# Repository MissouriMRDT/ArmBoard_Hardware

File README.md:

# RoboticArm-Hardware
Hardware design files for robotic arm

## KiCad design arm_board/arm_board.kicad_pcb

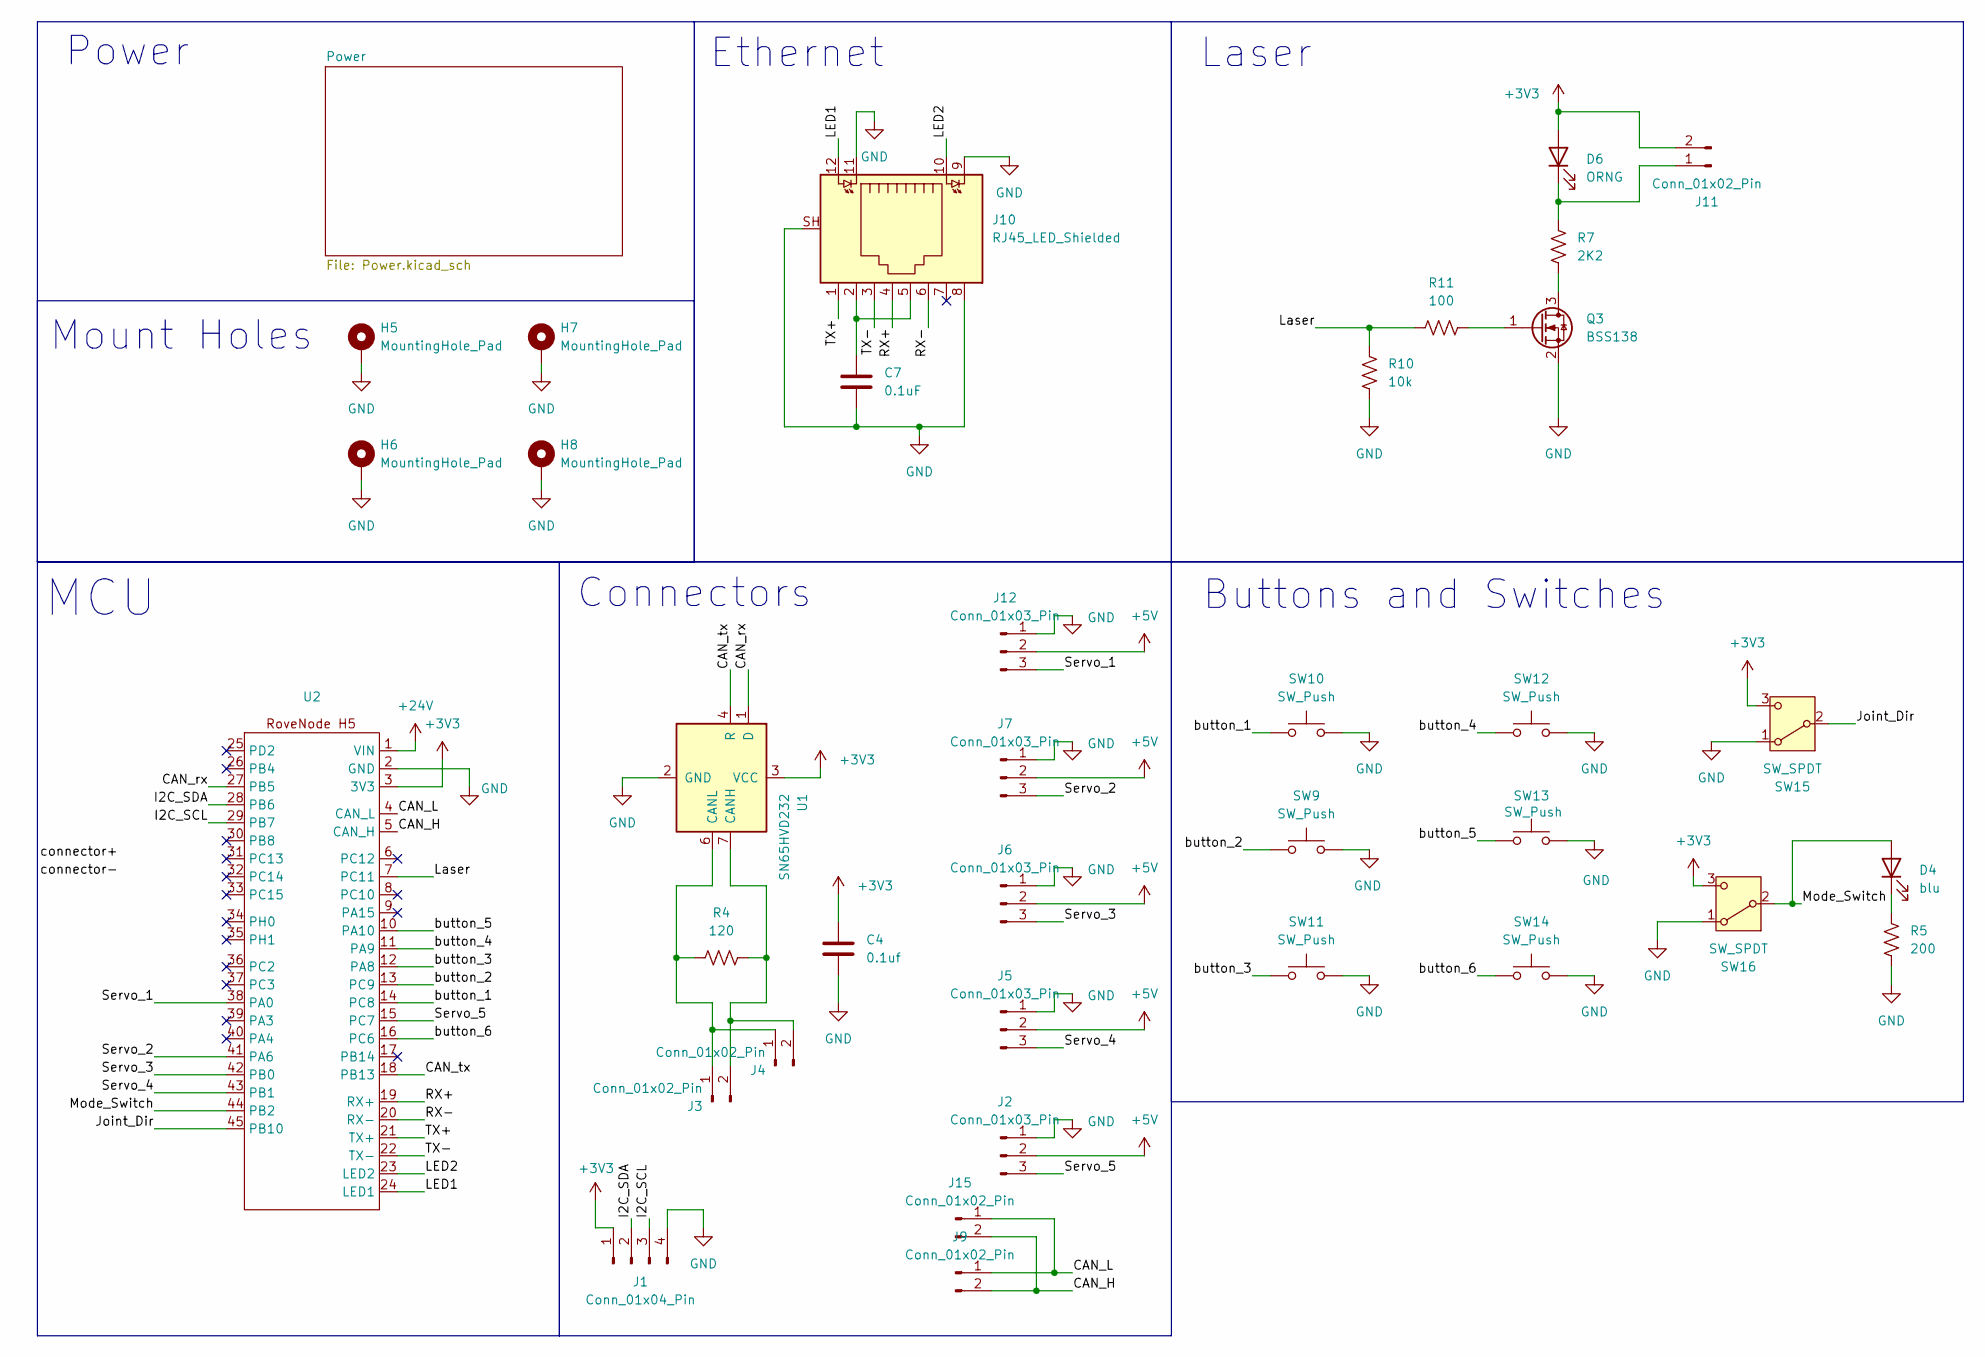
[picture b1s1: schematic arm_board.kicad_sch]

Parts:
C4: 0.1uf; C_0603_1608Metric_Pad1.08x0.95mm_HandSolder
C7: 0.1uF; C_0603_1608Metric_Pad1.08x0.95mm_HandSolder
D4: blu; LED_0603_1608Metric_Pad1.05x0.95mm_HandSolder
D6: ORNG; LED_0603_1608Metric_Pad1.05x0.95mm_HandSolder
H5, H6, H7, H8: MountingHole_Pad; 4_40_Hole_Pad_Via
J1: Conn_01x04_Pin; JST_PH_S4B-PH-K_1x04_P2.00mm_Horizontal
J2, J5, J6, J7, J12: Conn_01x03_Pin; JST_PH_S3B-PH-K_1x03_P2.00mm_Horizontal
J3, J4, J9, J11, J15: Conn_01x02_Pin; JST_PH_S2B-PH-K_1x02_P2.00mm_Horizontal
J10: RJ45_LED_Shielded; RJ45_Teensy
Q3: BSS138; SOT-23
R4: 120; R_0603_1608Metric_Pad0.98x0.95mm_HandSolder
R5: 200; R_0603_1608Metric_Pad0.98x0.95mm_HandSolder
R7: 2K2; R_0603_1608Metric_Pad0.98x0.95mm_HandSolder
R10: 10k; R_0603_1608Metric_Pad0.98x0.95mm_HandSolder
R11: 100; R_0603_1608Metric_Pad0.98x0.95mm_HandSolder
SW9, SW10, SW11, SW12, SW13, SW14: SW_Push; SW_SPST_TL3305A
SW15, SW16: SW_SPDT; SW_Slide_SPDT_Angled_CK_OS102011MA1Q
U1: SN65HVD232; SOIC-8_3.9x4.9mm_P1.27mm
U2: RoveNode_H5

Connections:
+3V3: C4.1, D6.2 (A), J1.1, J11.2, SW15.3 (C), SW16.3 (C), U1.3 (VCC), U2.3 (3V3)
+5V: J2.2, J5.2, J6.2, J7.2, J12.2; also elsewhere on the board
+24V: U2.1 (VIN); also elsewhere on the board
/CAN_H: J9.2, J15.2, U2.5 (CAN_H)
/CAN_L: J9.1, J15.1, U2.4 (CAN_L)
/CAN_rx: U1.1 (D), U2.27 (PB5)
/CAN_tx: U1.4 (R), U2.18 (PB13)
/I2C_SCL: J1.3, U2.29 (PB7)
/I2C_SDA: J1.2, U2.28 (PB6)
/Joint_Dir: SW15.2 (B), U2.45 (PB10)
/LED1: J10.12, U2.24 (LED1)
/LED2: J10.10, U2.23 (LED2)
/Laser: R10.1, R11.1, U2.7 (PC11)
/Mode_Switch: D4.2 (A), SW16.2 (B), U2.44 (PB2)
/RX+: J10.4, U2.19 (RX+)
/RX-: J10.6, U2.20 (RX-)
/Servo_1: J12.3, U2.38 (PA0)
/Servo_2: J7.3, U2.41 (PA6)
/Servo_3: J6.3, U2.42 (PB0)
/Servo_4: J5.3, U2.43 (PB1)
/Servo_5: J2.3, U2.15 (PC7)
/TX+: J10.1, U2.21 (TX+)
/TX-: J10.3, U2.22 (TX-)
/button_1: SW10.1, U2.14 (PC8)
/button_2: SW9.1, U2.13 (PC9)
/button_3: SW11.1, U2.12 (PA8)
/button_4: SW12.1, U2.11 (PA9)
/button_5: SW13.1, U2.10 (PA10)
/button_6: SW14.1, U2.16 (PC6)
GND: C4.2, C7.2, H5.1 (1_1), H6.1 (1_1), H7.1 (1_1), H8.1 (1_1), J1.4, J2.1, J5.1, J6.1, J7.1, J10.8, J10.9, J10.11, J10.SH, J12.1, Q3.2 (S), R5.2, R10.2, SW9.2, SW10.2, SW11.2, SW12.2, SW13.2, SW14.2, SW15.1 (A), SW16.1 (A), U1.2 (GND), U2.2 (GND); also elsewhere on the board
unnamed: C7.1, J10.2, J10.5
unnamed: D4.1 (K), R5.1
unnamed: D6.1 (K), J11.1, R7.1
unnamed: J3.1, J4.1, R4.2, U1.6 (CANL)
unnamed: J3.2, J4.2, R4.1, U1.7 (CANH)
unnamed: Q3.3 (D), R7.2
unnamed: Q3.1 (G), R11.2

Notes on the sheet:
Power
Connectors
Ethernet
MCU
Laser
Buttons and Switches
Mount Holes

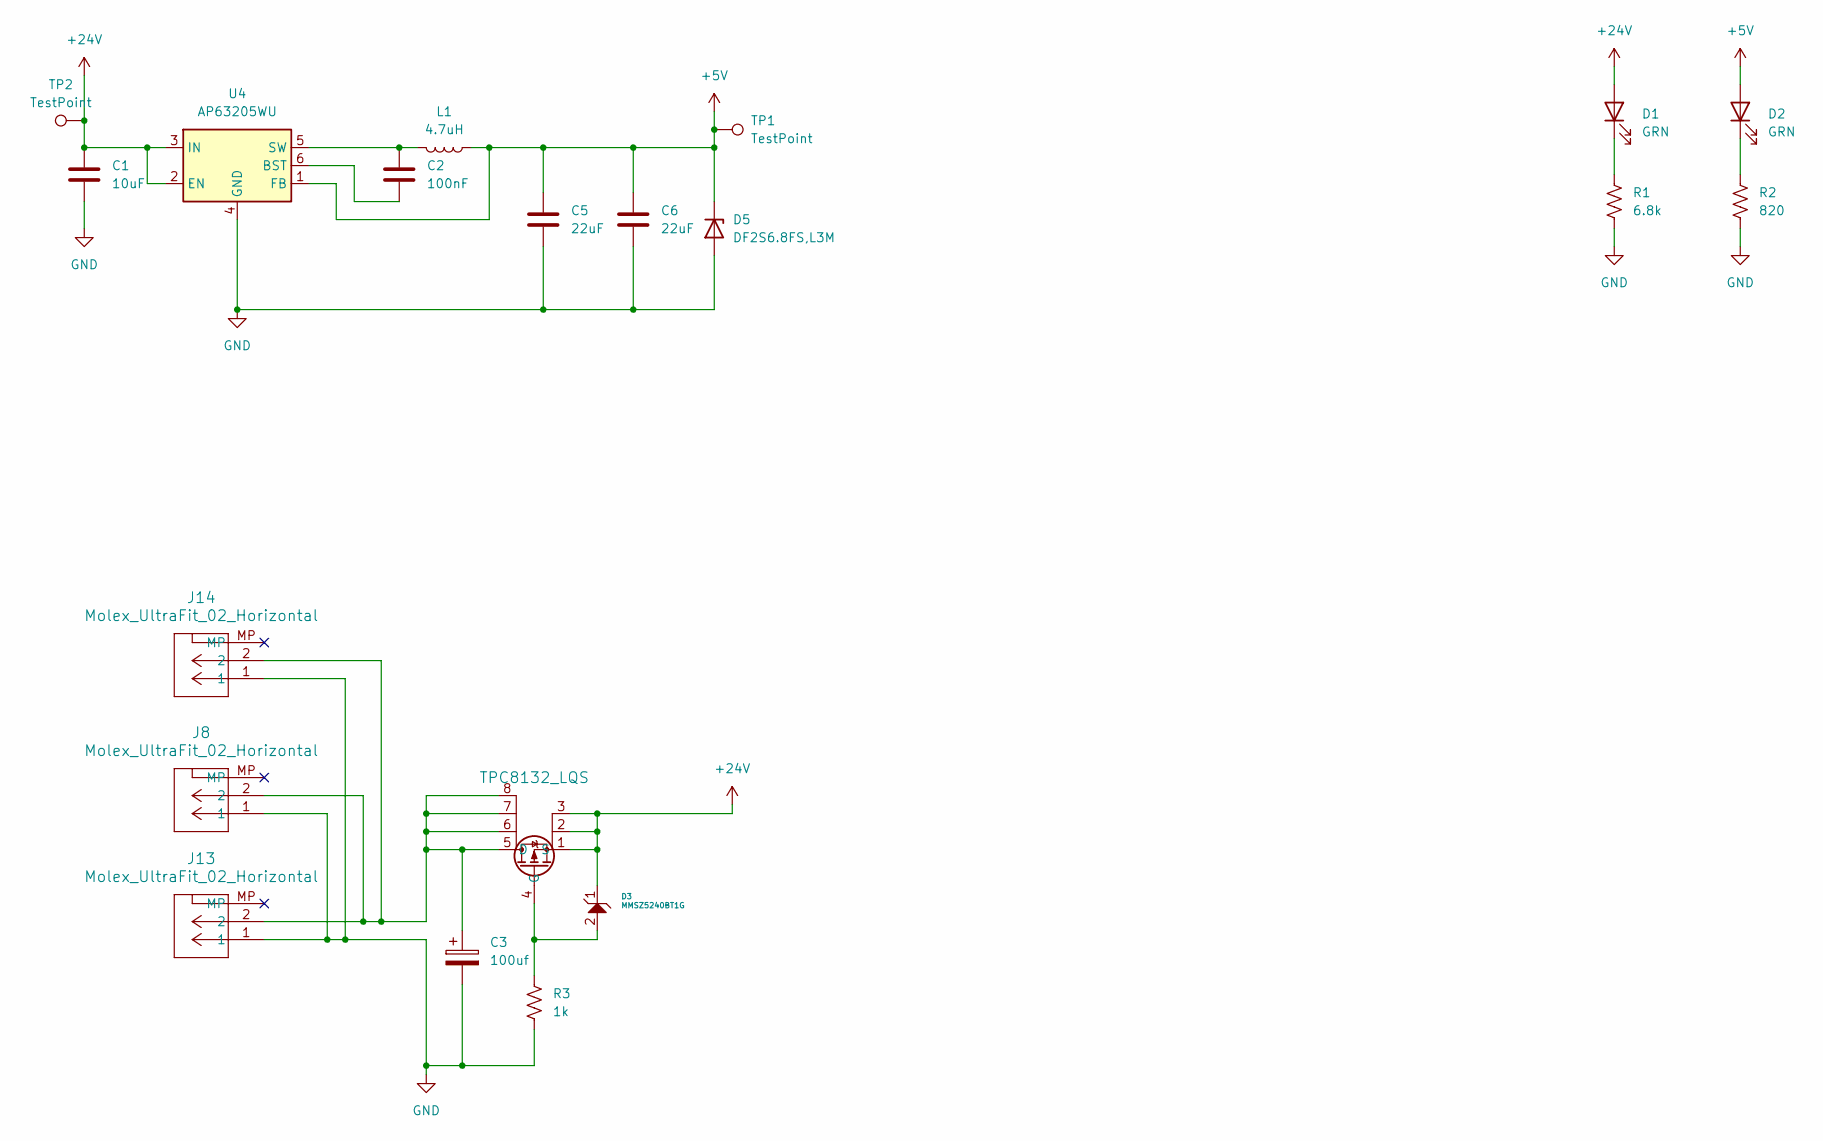
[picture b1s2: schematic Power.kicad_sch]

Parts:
C1: 10uF; C_0603_1608Metric_Pad1.08x0.95mm_HandSolder
C2: 100nF; C_0603_1608Metric_Pad1.08x0.95mm_HandSolder
C3: 100uf; CP_Radial_D6.3mm_P2.50mm
C5, C6: 22uF; C_0603_1608Metric_Pad1.08x0.95mm_HandSolder
D1, D2: GRN; LED_0603_1608Metric_Pad1.05x0.95mm_HandSolder
D3: MMSZ5240BT1G; SOD-123_ONS-L
D5: DF2S6.8FS,L3M; SOD-323_1P8X1P35_ONS
J8, J13, J14: Molex_UltraFit_02_Horizontal; MOLEX_MegaFit_02_Horizontal; MPN 1723102000
L1: 4.7uH; IND_DFE322520FD-4R7M=P2_MUR
MOSFET1: TPC8132_LQS; SOP-8_TOS-L
R1: 6.8k; R_0603_1608Metric_Pad0.98x0.95mm_HandSolder
R2: 820; R_0603_1608Metric_Pad0.98x0.95mm_HandSolder
R3: 1k; R_0603_1608Metric_Pad0.98x0.95mm_HandSolder
TP1, TP2: TestPoint; TestPoint_Pad_1.5x1.5mm
U4: AP63205WU; TSOT-23-6_HandSoldering

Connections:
+5V: C5.1, C6.1, D2.2 (A), D5.1 (K), L1.1, TP1.1 (1_1), U4.1 (FB); also elsewhere on the board
+24V: C1.1, D1.2 (A), D3.1, MOSFET1.1 (S), MOSFET1.2, MOSFET1.3, TP2.1 (1_1), U4.2 (EN), U4.3 (IN); also elsewhere on the board
GND: C1.2, C3.2, C5.2, C6.2, D5.2 (A), J8.1, J13.1, J14.1, R1.2, R2.2, R3.2, U4.4 (GND); also elsewhere on the board
unnamed: D1.1 (K), R1.1
unnamed: D2.1 (K), R2.1
unnamed: C3.1, J8.2, J13.2, J14.2, MOSFET1.5 (D), MOSFET1.6, MOSFET1.7, MOSFET1.8
unnamed: D3.2, MOSFET1.4 (G), R3.1
unnamed: C2.2, U4.6 (BST)
unnamed: C2.1, L1.2, U4.5 (SW)

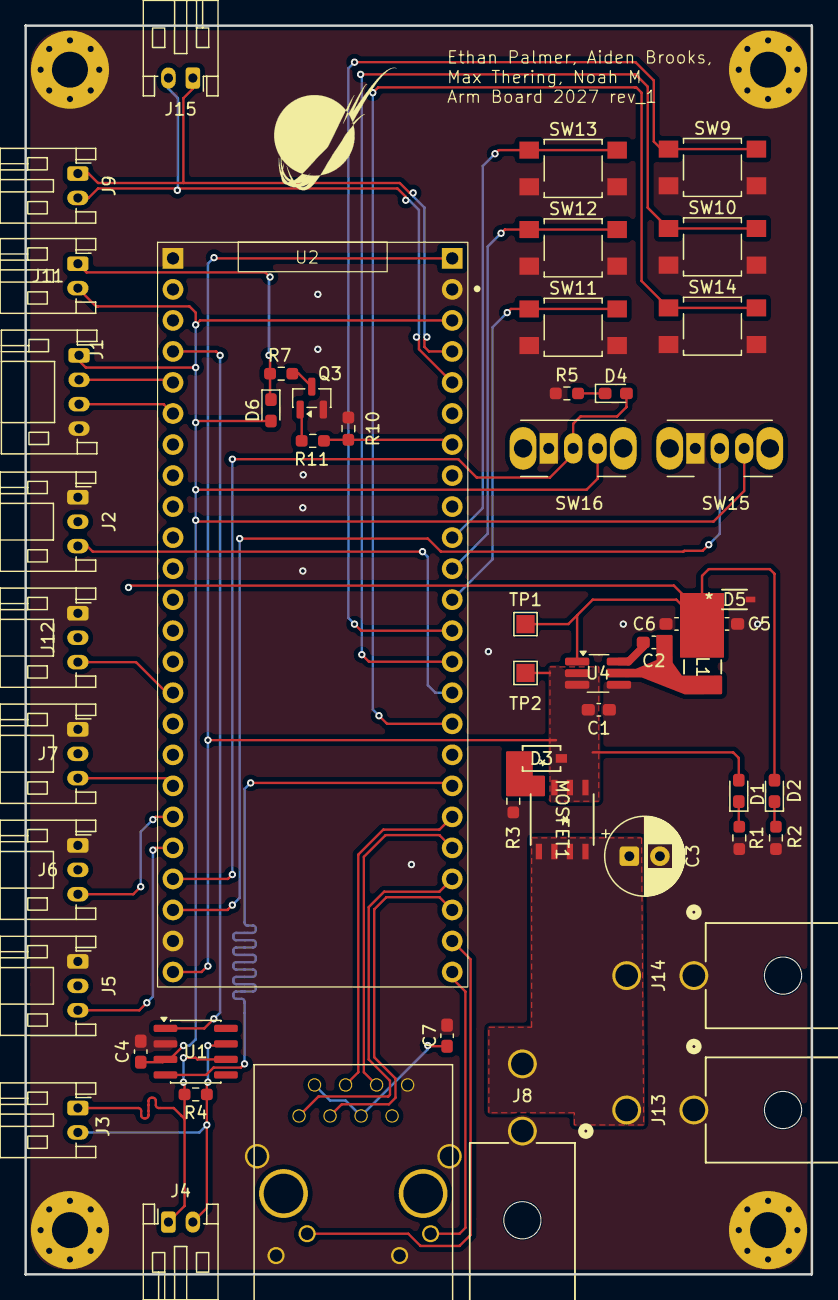
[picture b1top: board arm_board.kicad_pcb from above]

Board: 2 copper layers, 64.4 x 102.2 mm, 56 parts (0 on the bottom side), 43 nets.

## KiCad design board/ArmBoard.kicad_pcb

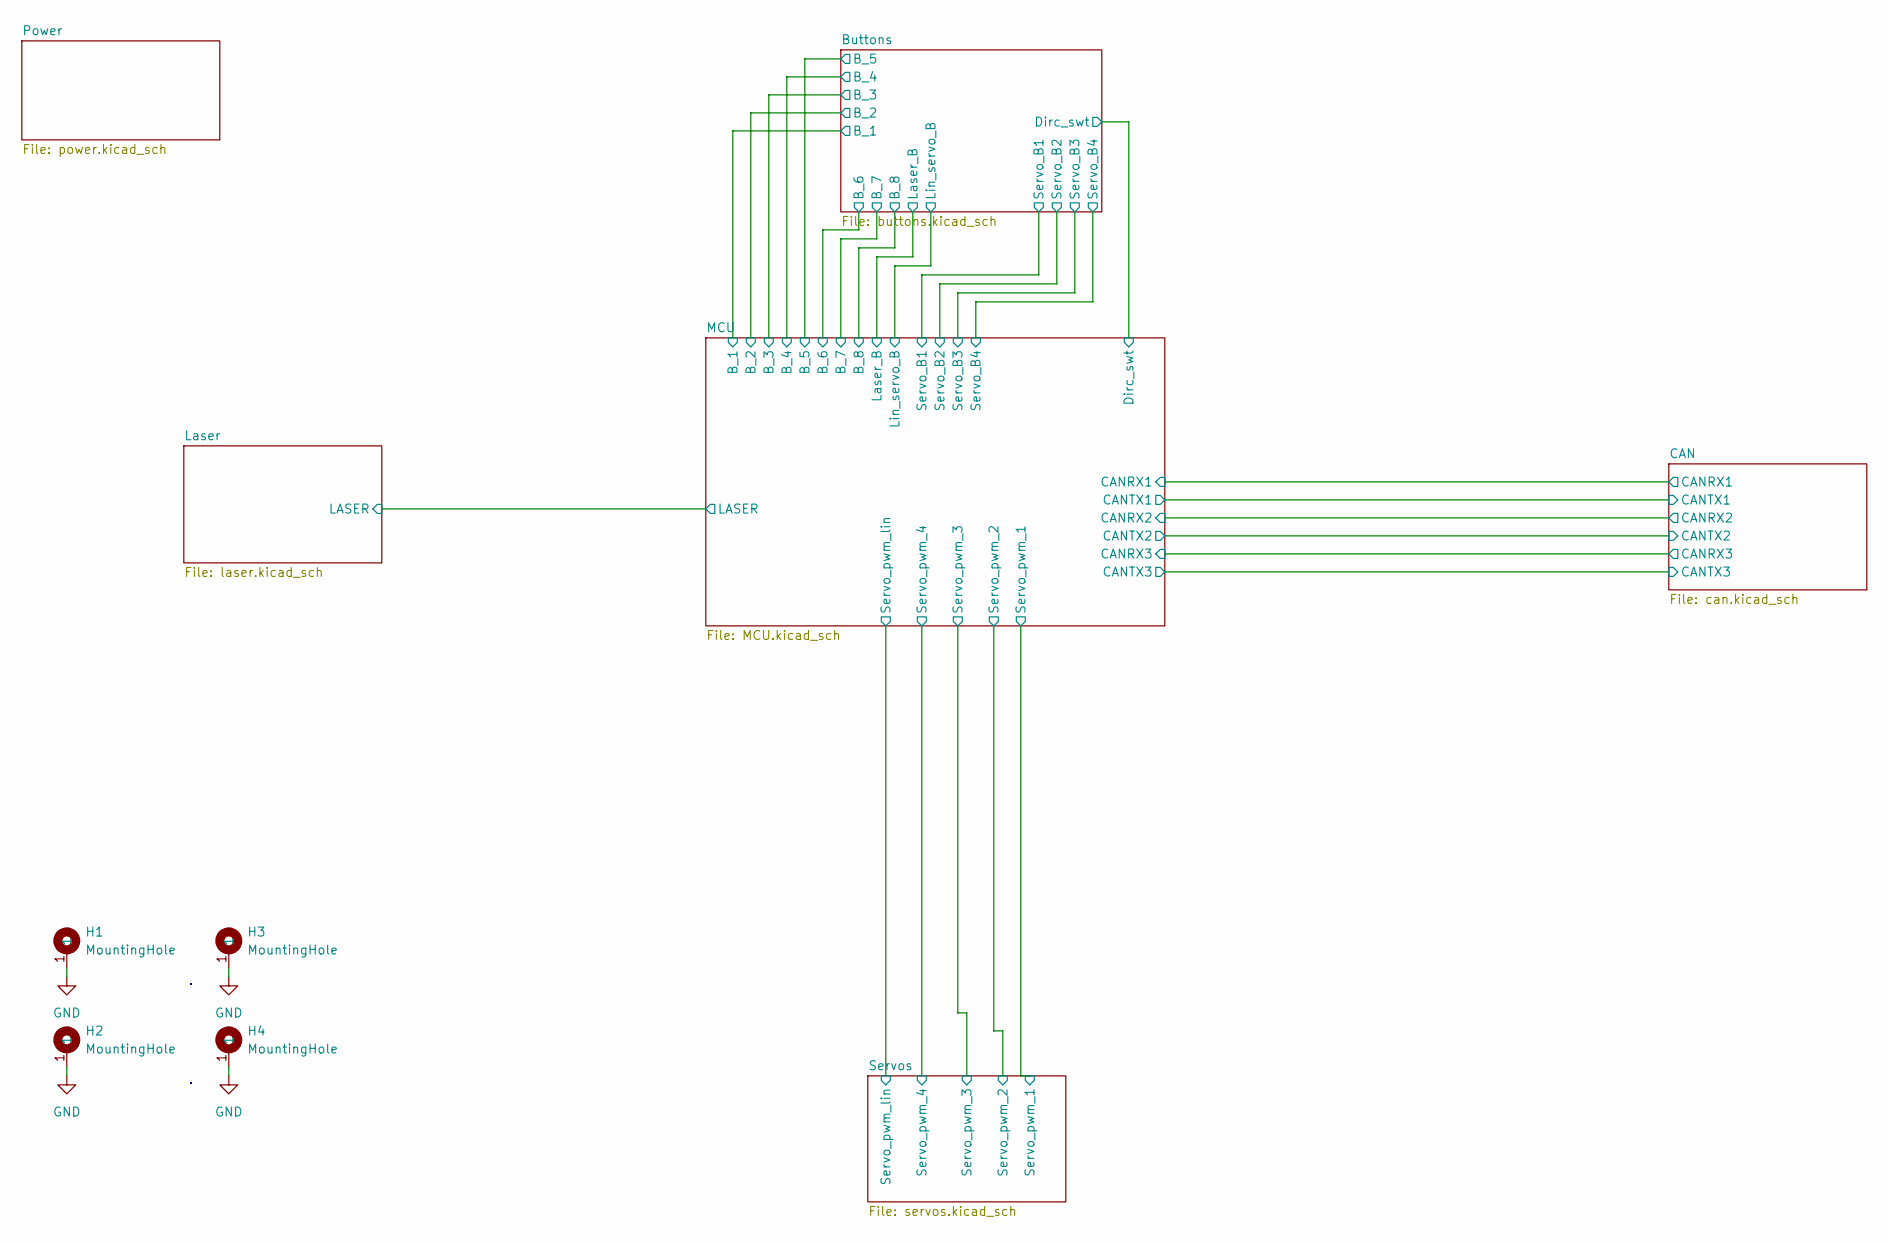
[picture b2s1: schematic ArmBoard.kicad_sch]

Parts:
H1, H2, H3, H4: MountingHole; 4_40_Hole_Pad_Via

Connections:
GND: H1.1, H2.1, H3.1, H4.1; also elsewhere on the board

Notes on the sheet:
Penis

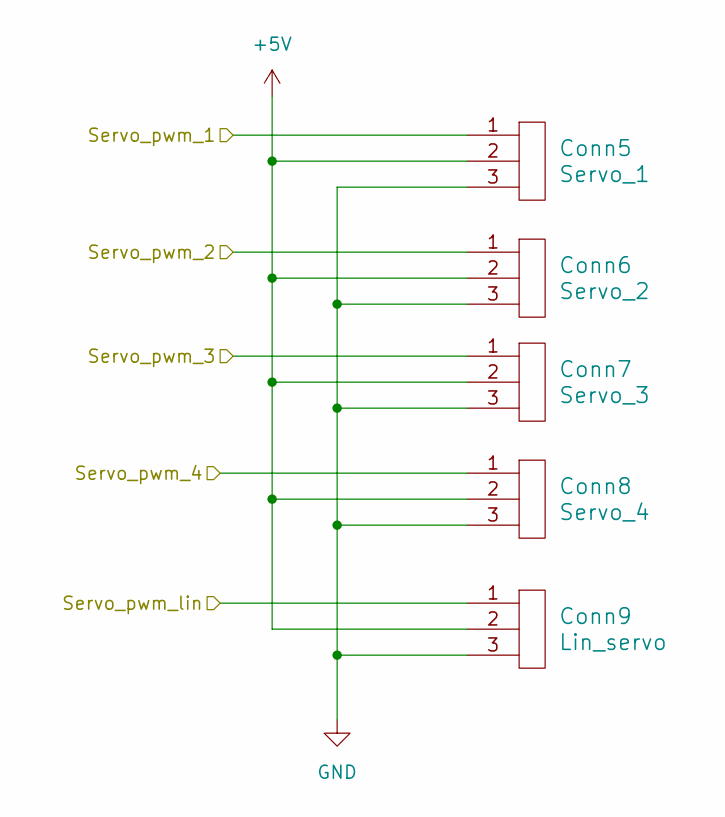
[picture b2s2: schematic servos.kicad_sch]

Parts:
Conn5: Servo_1; MOLEX_SL_03_Vertical
Conn6: Servo_2; MOLEX_SL_03_Vertical
Conn7: Servo_3; MOLEX_SL_03_Vertical
Conn8: Servo_4; MOLEX_SL_03_Vertical
Conn9: Lin_servo; MOLEX_SL_03_Vertical

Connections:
+5V: Conn5.2, Conn6.2, Conn7.2, Conn8.2, Conn9.2; also elsewhere on the board
/MCU/Servo_pwm_1: Conn5.1; also elsewhere on the board
/MCU/Servo_pwm_2: Conn6.1; also elsewhere on the board
/MCU/Servo_pwm_3: Conn7.1; also elsewhere on the board
/MCU/Servo_pwm_4: Conn8.1; also elsewhere on the board
/MCU/Servo_pwm_lin: Conn9.1; also elsewhere on the board
GND: Conn5.3, Conn6.3, Conn7.3, Conn8.3, Conn9.3; also elsewhere on the board

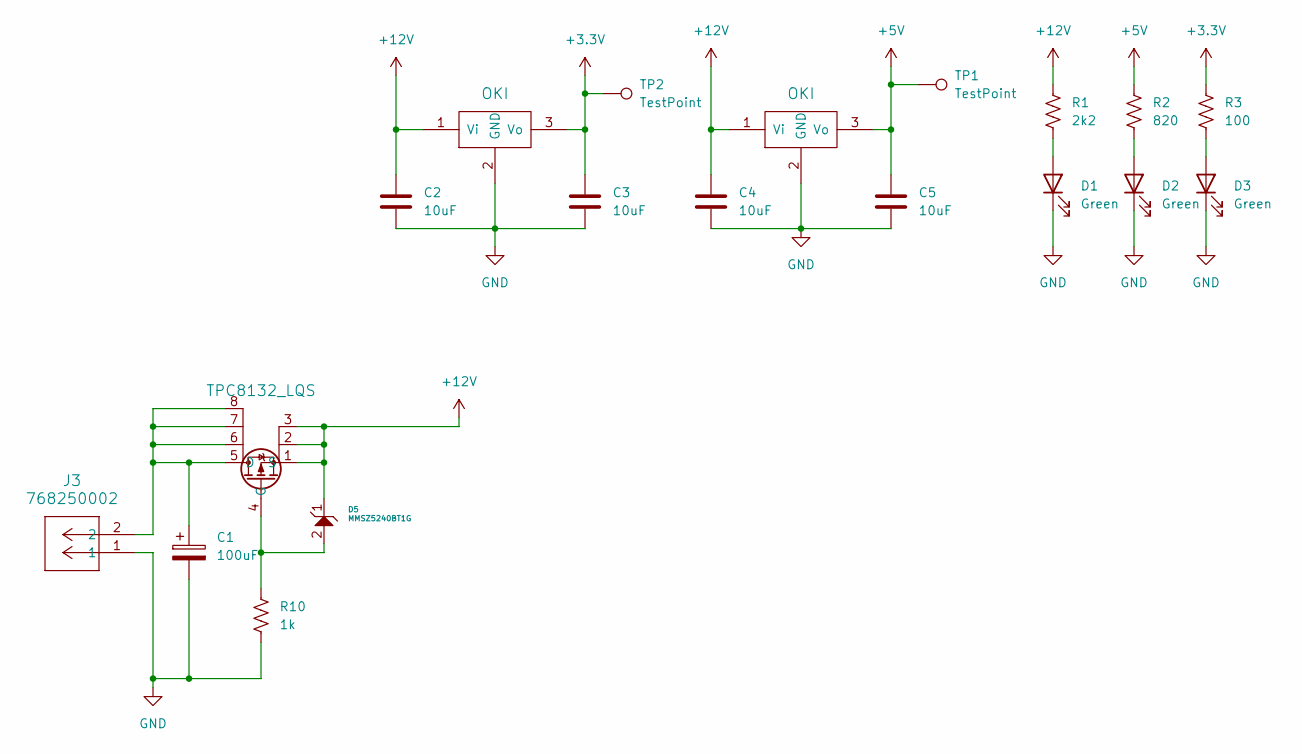
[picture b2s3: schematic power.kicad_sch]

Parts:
C1: 100uF; CP_Radial_D6.3mm_P2.50mm
C2, C3, C4, C5: 10uF; C_0603_1608Metric_Pad1.08x0.95mm_HandSolder
D1, D2, D3: Green; LED_0603_1608Metric_Pad1.05x0.95mm_HandSolder
D5: MMSZ5240BT1G; SOD-123_ONS-L
J3: 768250002; MOLEX_MegaFit_02_Horizontal
MOSFET1: TPC8132_LQS; SOP-8_TOS-L
R1: 2k2; R_0603_1608Metric_Pad0.98x0.95mm_HandSolder
R2: 820; R_0603_1608Metric_Pad0.98x0.95mm_HandSolder
R3: 100; R_0603_1608Metric_Pad0.98x0.95mm_HandSolder
R10: 1k; R_0603_1608Metric_Pad0.98x0.95mm_HandSolder
TP1, TP2: TestPoint; TestPoint_Pad_1.5x1.5mm
U2, U3: OKI; OKI_Horizontal

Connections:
+3.3V: C3.1, R3.1, TP2.1, U2.3 (Vo); also elsewhere on the board
+5V: C5.1, R2.1, TP1.1, U3.3 (Vo); also elsewhere on the board
+12V: C2.1, C4.1, D5.1, MOSFET1.1 (S), MOSFET1.2, MOSFET1.3, R1.1, U2.1 (Vi), U3.1 (Vi)
GND: C1.2, C2.2, C3.2, C4.2, C5.2, D1.1 (K), D2.1 (K), D3.1 (K), J3.1, R10.2, U2.2 (GND), U3.2 (GND); also elsewhere on the board
unnamed: D1.2 (A), R1.2
unnamed: D2.2 (A), R2.2
unnamed: D3.2 (A), R3.2
unnamed: C1.1, J3.2, MOSFET1.5 (D), MOSFET1.6, MOSFET1.7, MOSFET1.8
unnamed: D5.2, MOSFET1.4 (G), R10.1

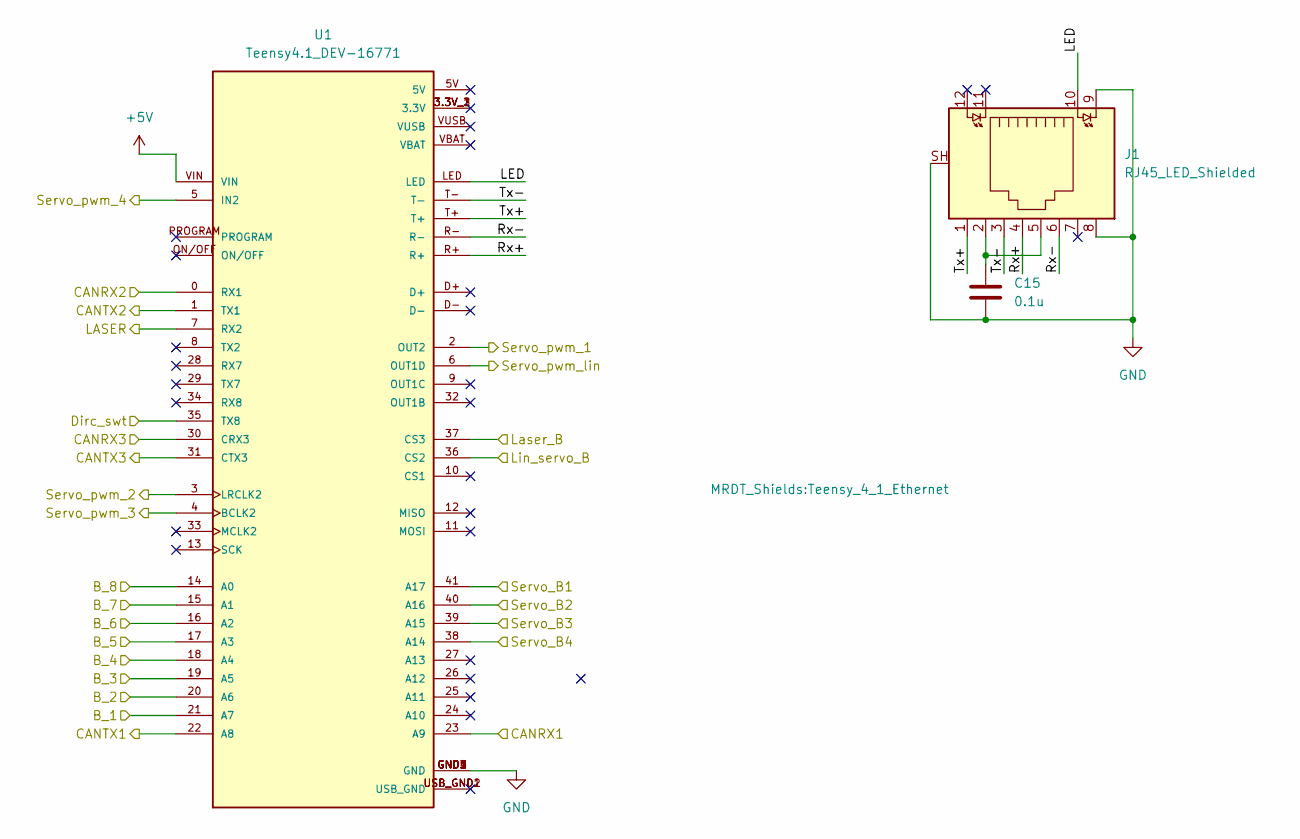
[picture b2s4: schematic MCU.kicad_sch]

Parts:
C15: 0.1u; C_0603_1608Metric_Pad1.08x0.95mm_HandSolder
J1: RJ45_LED_Shielded; RJ45_Teensy
U1: Teensy4.1_DEV-16771; Teensy_4_1_Ethernet; PARTREV 4.1

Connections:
+5V: U1.VIN; also elsewhere on the board
/Buttons/B_1: U1.21 (A7); also elsewhere on the board
/Buttons/B_2: U1.20 (A6); also elsewhere on the board
/Buttons/B_3: U1.19 (A5); also elsewhere on the board
/Buttons/B_4: U1.18 (A4); also elsewhere on the board
/Buttons/B_5: U1.17 (A3); also elsewhere on the board
/Buttons/B_6: U1.16 (A2); also elsewhere on the board
/Buttons/B_7: U1.15 (A1); also elsewhere on the board
/Buttons/B_8: U1.14 (A0); also elsewhere on the board
/Buttons/Dirc_swt: U1.35 (TX8); also elsewhere on the board
/Buttons/Laser_B: U1.37 (CS3); also elsewhere on the board
/Buttons/Lin_servo_B: U1.36 (CS2); also elsewhere on the board
/Buttons/Servo_B1: U1.41 (A17); also elsewhere on the board
/Buttons/Servo_B2: U1.40 (A16); also elsewhere on the board
/Buttons/Servo_B3: U1.39 (A15); also elsewhere on the board
/Buttons/Servo_B4: U1.38 (A14); also elsewhere on the board
/CAN/CANRX1: U1.23 (A9); also elsewhere on the board
/CAN/CANRX2: U1.0 (RX1); also elsewhere on the board
/CAN/CANRX3: U1.30 (CRX3); also elsewhere on the board
/CAN/CANTX1: U1.22 (A8); also elsewhere on the board
/CAN/CANTX2: U1.1 (TX1); also elsewhere on the board
/CAN/CANTX3: U1.31 (CTX3); also elsewhere on the board
/Laser/LASER: U1.7 (RX2); also elsewhere on the board
/MCU/LED: J1.10, U1.LED
/MCU/Rx+: J1.4, U1.R+
/MCU/Rx-: J1.6, U1.R-
/MCU/Servo_pwm_1: U1.2 (OUT2); also elsewhere on the board
/MCU/Servo_pwm_2: U1.3 (LRCLK2); also elsewhere on the board
/MCU/Servo_pwm_3: U1.4 (BCLK2); also elsewhere on the board
/MCU/Servo_pwm_4: U1.5 (IN2); also elsewhere on the board
/MCU/Servo_pwm_lin: U1.6 (OUT1D); also elsewhere on the board
/MCU/Tx+: J1.1, U1.T+
/MCU/Tx-: J1.3, U1.T-
GND: C15.2, J1.8, J1.9, J1.SH, U1.GND1 (GND), U1.GND2 (GND), U1.GND3 (GND), U1.GND4 (GND), U1.GND5 (GND); also elsewhere on the board
unnamed: C15.1, J1.2, J1.5

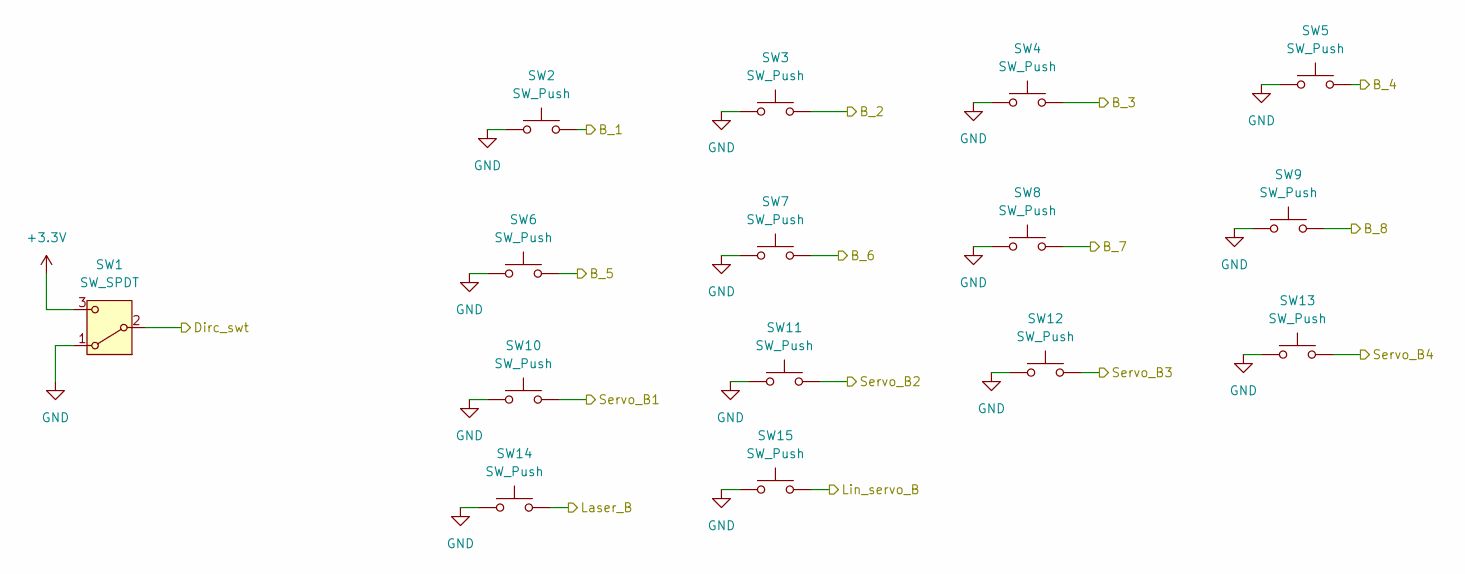
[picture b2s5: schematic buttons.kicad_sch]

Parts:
SW1: SW_SPDT; SW_Slide_SPDT_Angled_CK_OS102011MA1Q
SW2, SW3, SW4, SW5, SW6, SW7, SW8, SW9, SW10, SW11, SW12, SW13, SW14, SW15: SW_Push; SW_SPST_TL3305A

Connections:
+3.3V: SW1.3 (C); also elsewhere on the board
/Buttons/B_1: SW2.2; also elsewhere on the board
/Buttons/B_2: SW3.2; also elsewhere on the board
/Buttons/B_3: SW4.2; also elsewhere on the board
/Buttons/B_4: SW5.2; also elsewhere on the board
/Buttons/B_5: SW6.2; also elsewhere on the board
/Buttons/B_6: SW7.2; also elsewhere on the board
/Buttons/B_7: SW8.2; also elsewhere on the board
/Buttons/B_8: SW9.2; also elsewhere on the board
/Buttons/Dirc_swt: SW1.2 (B); also elsewhere on the board
/Buttons/Laser_B: SW14.2; also elsewhere on the board
/Buttons/Lin_servo_B: SW15.2; also elsewhere on the board
/Buttons/Servo_B1: SW10.2; also elsewhere on the board
/Buttons/Servo_B2: SW11.2; also elsewhere on the board
/Buttons/Servo_B3: SW12.2; also elsewhere on the board
/Buttons/Servo_B4: SW13.2; also elsewhere on the board
GND: SW1.1 (A), SW2.1, SW3.1, SW4.1, SW5.1, SW6.1, SW7.1, SW8.1, SW9.1, SW10.1, SW11.1, SW12.1, SW13.1, SW14.1, SW15.1; also elsewhere on the board

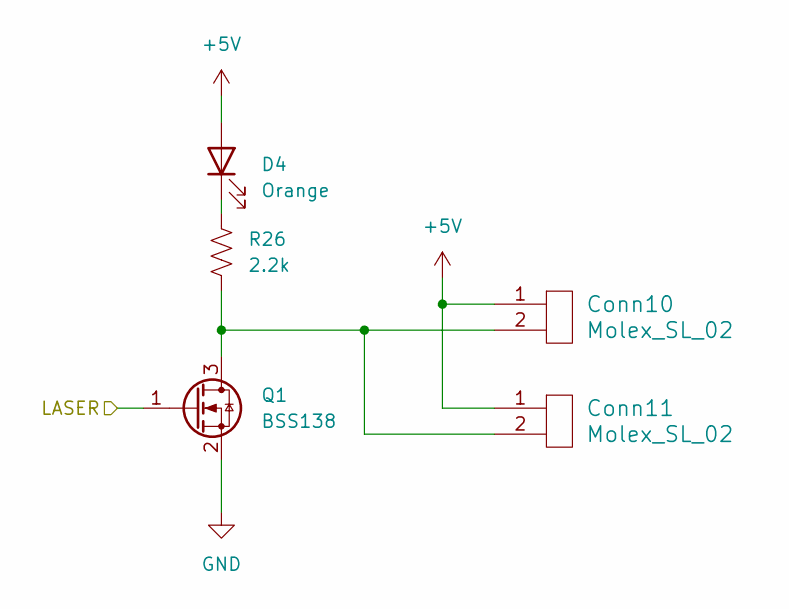
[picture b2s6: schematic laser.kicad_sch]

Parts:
Conn10, Conn11: Molex_SL_02; MOLEX_SL_02_Vertical
D4: Orange; LED_0603_1608Metric_Pad1.05x0.95mm_HandSolder
Q1: BSS138; SOT-23
R26: 2.2k; R_0603_1608Metric_Pad0.98x0.95mm_HandSolder

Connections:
+5V: Conn10.1, Conn11.1, D4.2 (A); also elsewhere on the board
/Laser/LASER: Q1.1 (G); also elsewhere on the board
GND: Q1.2 (S); also elsewhere on the board
unnamed: D4.1 (K), R26.1
unnamed: Conn10.2, Conn11.2, Q1.3 (D), R26.2

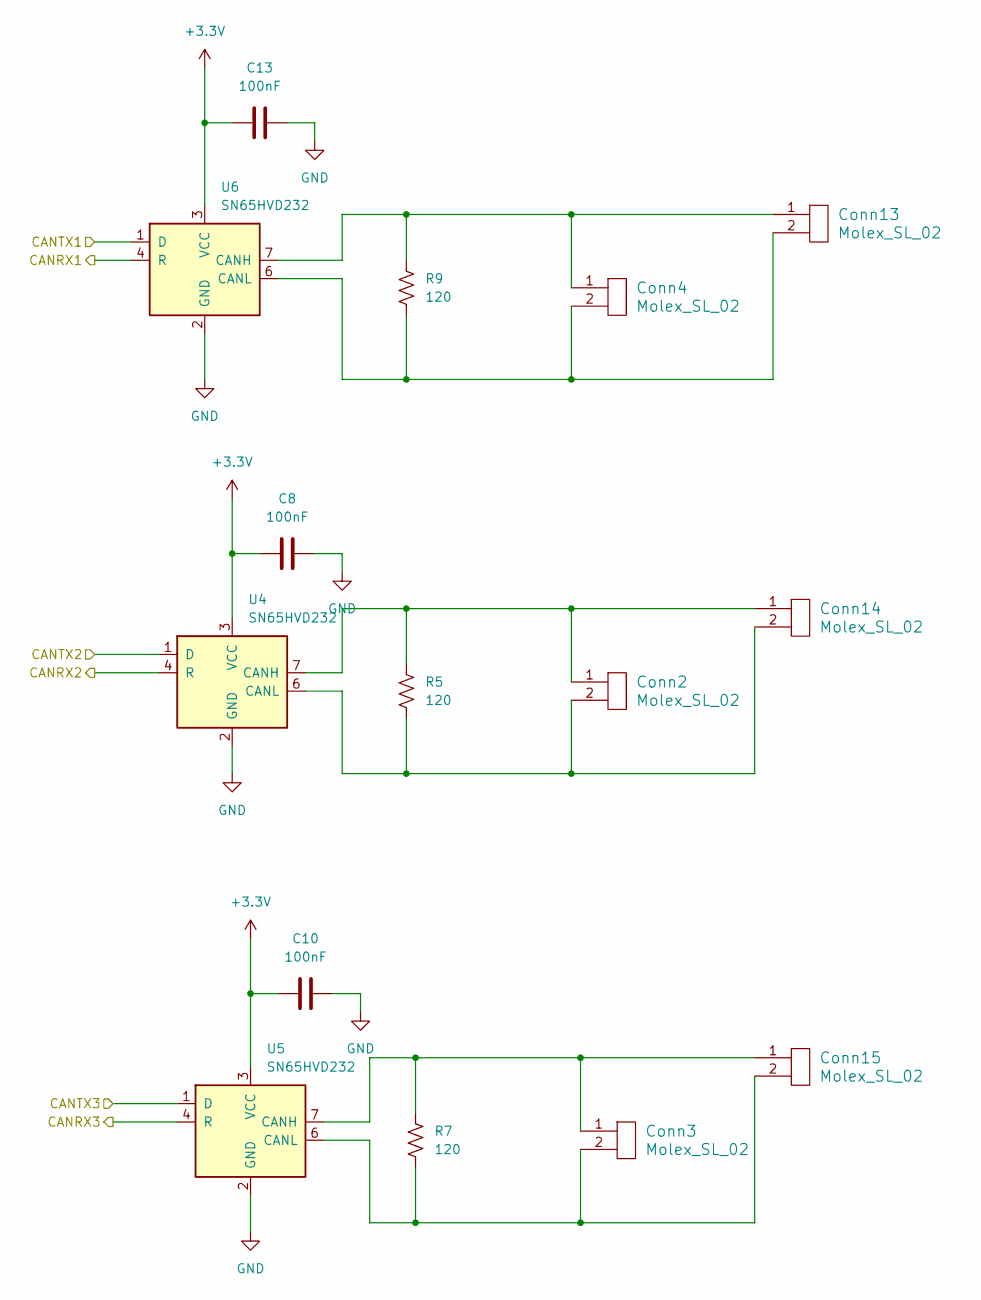
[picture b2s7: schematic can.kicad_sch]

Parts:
C8, C10, C13: 100nF; C_0603_1608Metric_Pad1.08x0.95mm_HandSolder
Conn2, Conn3, Conn4, Conn13, Conn14, Conn15: Molex_SL_02; MOLEX_SL_02_Vertical
R5, R7, R9: 120; R_0603_1608Metric_Pad0.98x0.95mm_HandSolder
U4, U5, U6: SN65HVD232; SOIC-8_3.9x4.9mm_P1.27mm

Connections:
+3.3V: C8.1, C10.1, C13.1, U4.3 (VCC), U5.3 (VCC), U6.3 (VCC); also elsewhere on the board
/CAN/CANRX1: U6.4 (R); also elsewhere on the board
/CAN/CANRX2: U4.4 (R); also elsewhere on the board
/CAN/CANRX3: U5.4 (R); also elsewhere on the board
/CAN/CANTX1: U6.1 (D); also elsewhere on the board
/CAN/CANTX2: U4.1 (D); also elsewhere on the board
/CAN/CANTX3: U5.1 (D); also elsewhere on the board
GND: C8.2, C10.2, C13.2, U4.2 (GND), U5.2 (GND), U6.2 (GND); also elsewhere on the board
unnamed: Conn2.1, Conn14.1, R5.1, U4.7 (CANH)
unnamed: Conn2.2, Conn14.2, R5.2, U4.6 (CANL)
unnamed: Conn3.1, Conn15.1, R7.1, U5.7 (CANH)
unnamed: Conn3.2, Conn15.2, R7.2, U5.6 (CANL)
unnamed: Conn4.1, Conn13.1, R9.1, U6.7 (CANH)
unnamed: Conn4.2, Conn13.2, R9.2, U6.6 (CANL)

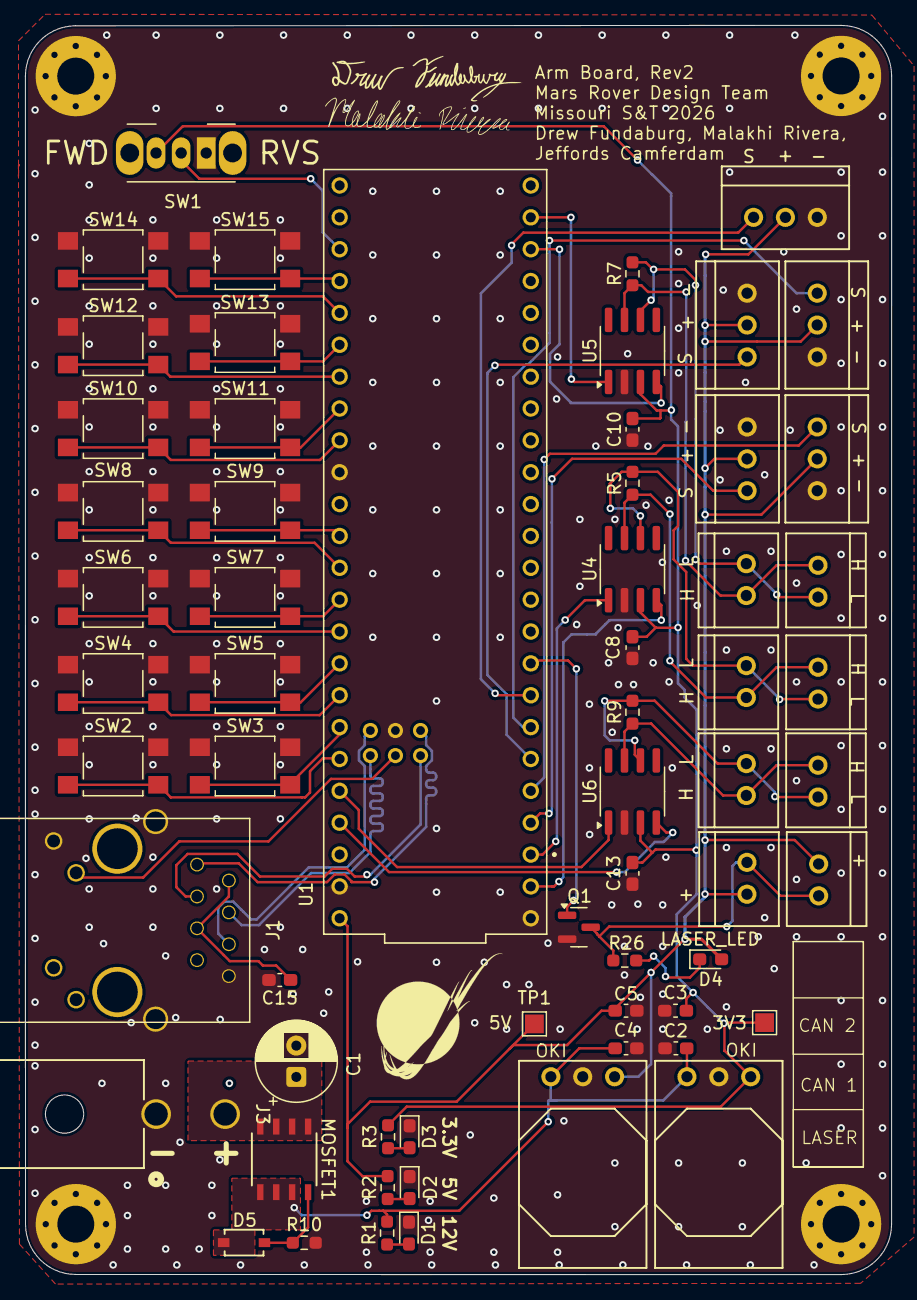
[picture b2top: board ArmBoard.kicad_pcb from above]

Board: 2 copper layers, 69.1 x 99.6 mm, 66 parts (0 on the bottom side), 50 nets.
